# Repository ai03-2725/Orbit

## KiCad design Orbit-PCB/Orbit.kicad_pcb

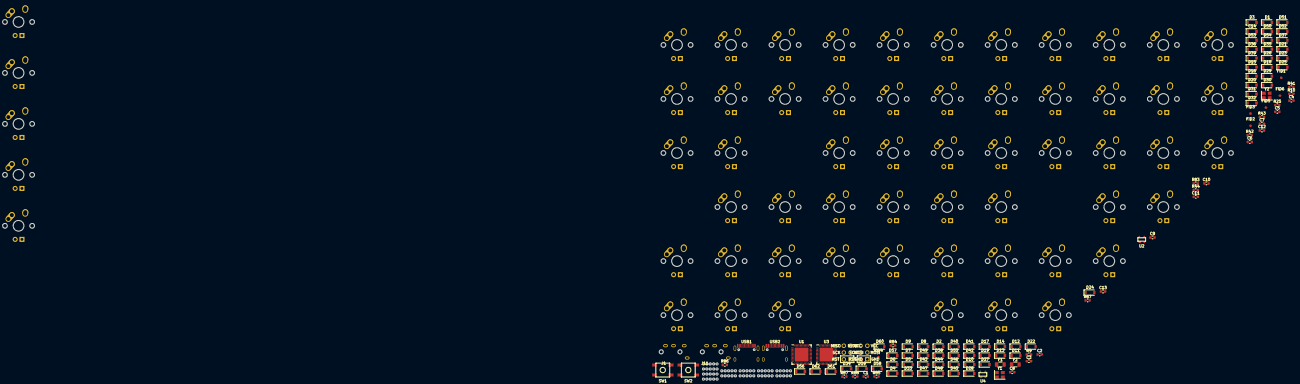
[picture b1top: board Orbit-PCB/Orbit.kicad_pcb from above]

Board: 2 copper layers, 184 parts (0 on the bottom side), 124 nets, no tracks yet.

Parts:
C1, C2, C8, C9: 22pF; C_0603_1608Metric
C3, C10: 1uF; C_0603_1608Metric
C4, C5, C6, C11, C12, C13: 0.1uF; C_0603_1608Metric
C7: 10uF; C_0603_1608Metric
C14: 10uF; D_SOD-123
D1, D2: Schottky; D_SOD-123
D3, D4, D5, D6, D7, D8, D9, D10, D11, D12, D13, D14, D15, D16, D17, D18, D19, D20, D21, D22, D23, D24, D25, D26, D27, D28, D29, D30, D31, D32, D33, D34, D35, D36, D37, D38, D39, D40, D41, D42, D43, D44, D45, D46, D47, D48, D49, D50, D51, D52, D53, D54, D55, D56, D57, D58, D59, D60, D61, D62: SOD-123; D_SOD-123
F1, F2: 500mA; Fuse_1206_3216Metric
FID1, FID2, FID3, FID4, FID5, FID6: Fiducial; Fiducial_1mm_Mask3mm
J1, J11: PJ-3200B-4A
J2, J12: AVR-ISP-6; Reset_Pretty-Mask
J3, J5, J6, J7, J9, J10, J13, J14, J17, J18, J19, J20: Breakaway_Tabs; breakaway-mousebites
MX1, MX2, MX3, MX4, MX5, MX6, MX7, MX8, MX9, MX10, MX11, MX12, MX13, MX14, MX15, MX16, MX17, MX18, MX19, MX20, MX21, MX22, MX23, MX24, MX25, MX26, MX27, MX28, MX29, MX30, MX31, MX32, MX33, MX34, MX35, MX36, MX37, MX38, MX39, MX40, MX41, MX42, MX43, MX44, MX45, MX46, MX47, MX48, MX49, MX50, MX51, MX52, MX53, MX54, MX55, MX56, MX57, MX58, MX59, MX60: MX-1U
R9, R10: 4.7k; R_0603_1608Metric
R25, R67, R87, R88: 10k; R_0603_1608Metric
R41, R42, R83, R84: 22; R_0603_1608Metric
R43, R44, R85, R86: 5.1k; R_0603_1608Metric
SW1, SW2: SW_Push; SKQGADE010
U1, U3: ATmega32U4-MU; QFN-44-1EP_7x7mm_P0.5mm_EP5.15x5.15mm
U2, U4: PRTR5V0U2X; SOT143B
USB1, USB2: HRO-TYPE-C-31-M-12; HRO-TYPE-C-31-M-12-Assembly
Y1, Y2: 16MHz; Crystal_SMD_3225-4Pin_3.2x2.5mm

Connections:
+5V: C4.1, C5.1, C6.1, C7.1, D1.1, J1.4, J2.2, R9.1, R10.1, R87.1, U1.14, U1.24, U1.34, U1.44
+5VA: C11.1, C12.1, C13.1, C14.1, D2.1, J11.4, J12.2, U3.14, U3.24, U3.34, U3.44
COL0: MX1.1, MX7.1, MX13.1, MX19.1, MX25.1, U1.32
COL0-R: MX31.1, MX37.1, MX43.1, MX49.1, MX55.1, U3.25
COL1: MX2.1, MX8.1, MX14.1, MX20.1, MX26.1, U1.28
COL1-R: MX32.1, MX38.1, MX44.1, MX50.1, MX56.1, U3.26
COL2: MX3.1, MX9.1, MX15.1, MX21.1, MX27.1, U1.27
COL2-R: MX33.1, MX39.1, MX45.1, MX51.1, MX57.1, U3.40
COL3: MX4.1, MX10.1, MX16.1, MX22.1, MX28.1, U1.26
COL3-R: MX34.1, MX40.1, MX46.1, MX52.1, MX58.1, U3.41
COL4: MX5.1, MX11.1, MX17.1, MX23.1, MX29.1, U1.25
COL4-R: MX35.1, MX41.1, MX47.1, MX53.1, MX59.1, U3.39
COL5: MX6.1, MX12.1, MX18.1, MX24.1, MX30.1, U1.40
COL5-R: MX36.1, MX42.1, MX48.1, MX54.1, MX60.1, U3.38
D+: R41.1, U1.4
D+-R: R83.1, U3.4
D-: R42.1, U1.3
D--R: R84.1, U3.3
GND: C1.2, C2.2, C3.2, C4.2, C5.2, C6.2, C7.2, J1.1, J2.6, R25.1, R43.2, R44.2, SW1.1, U1.5, U1.15, U1.23, U1.35, U1.43, U1.45, U2.1, USB1.1, USB1.12, USB1.13, Y1.2, Y1.4
GNDA: C8.2, C9.2, C10.2, C11.2, C12.2, C13.2, C14.2, J11.1, J12.6, R67.1, R85.2, R86.2, R88.1, SW2.1, U3.5, U3.15, U3.23, U3.35, U3.43, U3.45, U4.1, USB2.1, USB2.12, USB2.13, Y2.2, Y2.4
HDETECT: R87.2, U1.22
HDETECT-R: R88.2, U3.22
MISO: J2.1, U1.11
MISO-R: J12.1, U3.11
MOSI: J2.4, U1.10
MOSI-R: J12.4, U3.10
unnamed: C1.1, U1.17, Y1.1
unnamed: C2.1, U1.16, Y1.3
unnamed: C3.1, U1.6
unnamed: C8.1, U3.17, Y2.1
unnamed: C9.1, U3.16, Y2.3
unnamed: C10.1, U3.6
unnamed: D3.2, MX1.2
unnamed: D4.2, MX2.2
unnamed: D5.2, MX3.2
unnamed: D6.2, MX4.2
unnamed: D7.2, MX5.2
unnamed: D8.2, MX6.2
unnamed: D9.2, MX7.2
unnamed: D10.2, MX8.2
unnamed: D11.2, MX9.2
unnamed: D12.2, MX10.2
unnamed: D13.2, MX11.2
unnamed: D14.2, MX12.2
unnamed: D15.2, MX13.2
unnamed: D16.2, MX14.2
unnamed: D17.2, MX15.2
unnamed: D18.2, MX16.2
unnamed: D19.2, MX17.2
unnamed: D20.2, MX18.2
unnamed: D21.2, MX19.2
unnamed: D22.2, MX20.2
unnamed: D23.2, MX21.2
unnamed: D24.2, MX22.2
unnamed: D25.2, MX23.2
unnamed: D26.2, MX24.2
unnamed: D27.2, MX25.2
unnamed: D28.2, MX26.2
unnamed: D29.2, MX27.2
unnamed: D30.2, MX28.2
unnamed: D31.2, MX29.2
unnamed: D32.2, MX30.2
unnamed: D33.2, MX31.2
unnamed: D34.2, MX32.2
unnamed: D35.2, MX33.2
unnamed: D36.2, MX34.2
unnamed: D37.2, MX35.2
unnamed: D38.2, MX36.2
unnamed: D39.2, MX37.2
unnamed: D40.2, MX38.2
unnamed: D41.2, MX39.2
unnamed: D42.2, MX40.2
unnamed: D43.2, MX41.2
unnamed: D44.2, MX42.2
unnamed: D45.2, MX43.2
unnamed: D46.2, MX44.2
unnamed: D47.2, MX45.2
unnamed: D48.2, MX46.2
unnamed: D49.2, MX47.2
unnamed: D50.2, MX48.2
unnamed: D51.2, MX49.2
unnamed: D52.2, MX50.2
unnamed: D53.2, MX51.2
unnamed: D54.2, MX52.2
unnamed: D55.2, MX53.2
unnamed: D56.2, MX54.2
unnamed: D57.2, MX55.2
unnamed: D58.2, MX56.2
unnamed: D59.2, MX57.2
unnamed: D60.2, MX58.2
unnamed: D61.2, MX59.2
unnamed: D62.2, MX60.2
unnamed: R25.2, U1.33
unnamed: R41.2, U2.2, USB1.6, USB1.8
unnamed: R42.2, U2.3, USB1.5, USB1.7
unnamed: R43.1, USB1.10
unnamed: R44.1, USB1.4
unnamed: R67.2, U3.33
unnamed: R83.2, U4.2, USB2.6, USB2.8
unnamed: R84.2, U4.3, USB2.5, USB2.7
unnamed: R85.1, USB2.10
unnamed: R86.1, USB2.4
RESET: J2.5, SW1.2, U1.13
RESET-R: J12.5, SW2.2, U3.13
ROW0: D3.1, D4.1, D5.1, D6.1, D7.1, D8.1, U1.36
ROW0-R: D33.1, D34.1, D35.1, D36.1, D37.1, D38.1, U3.30
ROW1: D9.1, D10.1, D11.1, D12.1, D13.1, D14.1, U1.37
ROW1-R: D39.1, D40.1, D41.1, D42.1, D43.1, D44.1, U3.29
ROW2: D15.1, D16.1, D17.1, D18.1, D19.1, D20.1, U1.38
ROW2-R: D45.1, D46.1, D47.1, D48.1, D49.1, D50.1, U3.28
ROW3: D21.1, D22.1, D23.1, D24.1, D25.1, D26.1, U1.39
ROW3-R: D51.1, D52.1, D53.1, D54.1, D55.1, D56.1, U3.27
ROW4: D28.1, D29.1, D30.1, D31.1, D32.1, U1.21
ROW4-R: D58.1, D59.1, D60.1, D61.1, D62.1, U3.1
SCK: J2.3, U1.9
SCK-R: J12.3, U3.9
SCL: J1.2, R10.2, U1.18
SCL-R: J11.2, U3.18
SDA: J1.3, R9.2, U1.19
SDA-R: J11.3, U3.19
VBUS: D1.2, F1.1, U1.2, U1.7
VCC: F1.2, U2.4, USB1.2, USB1.11
VDC: D2.2, F2.1, U3.2, U3.7
VDD: F2.2, U4.4, USB2.2, USB2.11

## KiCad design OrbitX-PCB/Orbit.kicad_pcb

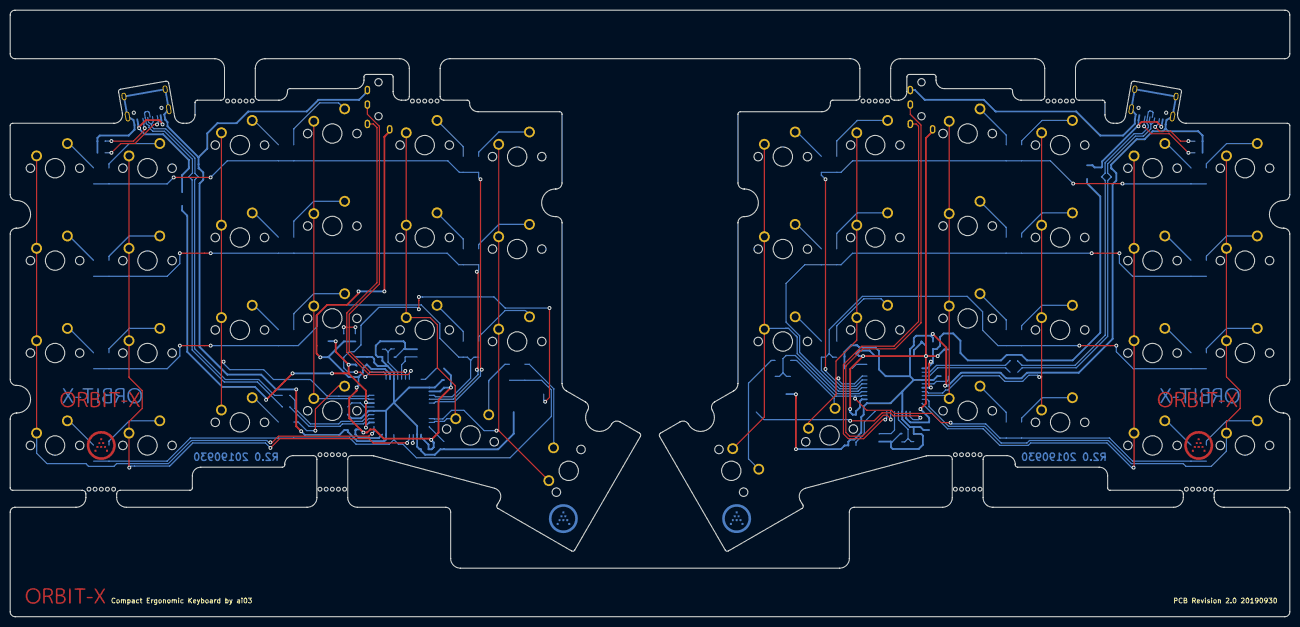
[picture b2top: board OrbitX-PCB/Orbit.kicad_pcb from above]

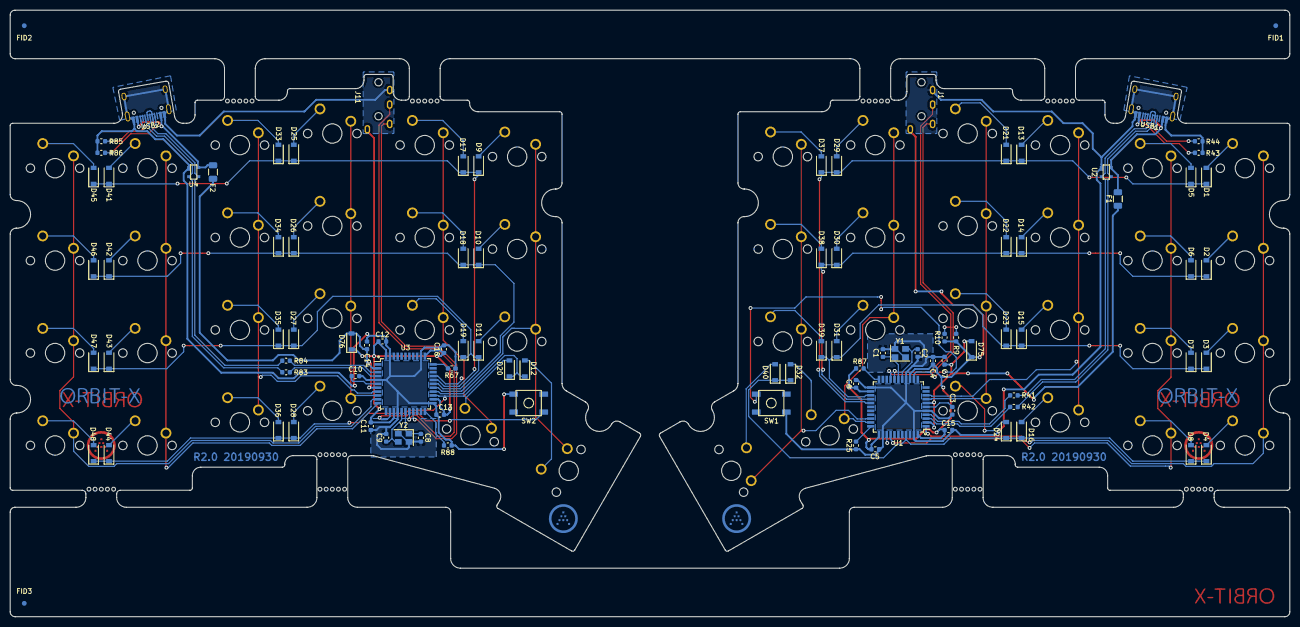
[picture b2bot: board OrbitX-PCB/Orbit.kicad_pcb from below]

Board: 2 copper layers, 263.8 x 125.0 mm, 155 parts (97 on the bottom side), 104 nets.

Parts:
C1, C2, C8, C9: 22pF; C_0603_1608Metric
C3, C10: 1uF; C_0603_1608Metric
C4, C5, C6, C11, C12, C13, C15, C16: 0.1uF; C_0603_1608Metric
C7, C14: 10uF; C_0603_1608Metric
D1, D2, D3, D4, D5, D6, D7, D8, D9, D10, D11, D12, D13, D14, D15, D16, D17, D18, D19, D20, D21, D22, D23, D24, D25, D26, D27, D28, D29, D30, D31, D32, D33, D34, D35, D36, D37, D38, D39, D40, D41, D42, D43, D44, D45, D46, D47, D48: SOD123; D_SOD-123
D75, D76: Schottky; D_SOD-123
F1, F2: 500mA; Fuse_1206_3216Metric
FID1, FID2, FID3: Fiducial; Fiducial_1mm_Dia_2.54mm_Outer_CopperTop
J1, J11: PJ-3200B-4A
J3, J5, J6, J7, J9, J13, J14, J17, J18, J19: Breakaway_Tabs; breakaway-mousebites
MX1, MX2, MX3, MX4, MX5, MX6, MX7, MX8, MX9, MX10, MX11, MX13, MX14, MX15, MX16, MX17, MX18, MX19, MX20, MX21, MX22, MX23, MX24, MX25, MX26, MX27, MX28, MX29, MX30, MX31, MX32, MX33, MX34, MX35, MX36, MX37, MX38, MX39, MX41, MX42, MX43, MX44, MX45, MX46, MX47, MX48: MX-NoLED; MXOnly-1U-NoLED
MX12, MX40: MX-NoLED; MXOnly-1.5U-NoLED
R9, R10: 4.7k; R_0603_1608Metric
R25, R67, R87, R88: 10k; R_0603_1608Metric
R41, R42, R83, R84: 22; R_0603_1608Metric
R43, R44, R85, R86: 5.1k; R_0603_1608Metric
SW1, SW2: SW_Push; SKQGADE010
U1, U3: ATmega32U4-AU; TQFP-44_10x10mm_P0.8mm
U2, U4: PRTR5V0U2X; SOT143B
USB1, USB2: HRO-TYPE-C-31-M-12; HRO-TYPE-C-31-M-12-Assembly
Y1, Y2: 16MHz; Crystal_SMD_3225-4Pin_3.2x2.5mm

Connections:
+5V: C4.1, C5.1, C6.1, C15.1, D75.1, J1.4, R9.1, R10.1, R87.1, U1.14, U1.24, U1.34, U1.44
+5VA: C11.1, C12.1, C13.1, C16.1, D76.1, J11.4, U3.14, U3.24, U3.34, U3.44
COL0: MX1.1, MX2.1, MX3.1, MX4.1, U1.1
COL0-R: MX9.1, MX10.1, MX11.1, MX12.1, U3.26
COL1: MX5.1, MX6.1, MX7.1, MX8.1, U1.37
COL1-R: MX17.1, MX18.1, MX19.1, MX20.1, U3.30
COL2: MX13.1, MX14.1, MX15.1, MX16.1, U1.9
COL2-R: MX25.1, MX26.1, MX27.1, MX28.1, U3.9
COL3: MX21.1, MX22.1, MX23.1, MX24.1, U1.8
COL3-R: MX33.1, MX34.1, MX35.1, MX36.1, U3.8
COL4: MX29.1, MX30.1, MX31.1, MX32.1, U1.32
COL4-R: MX41.1, MX42.1, MX43.1, MX44.1, U3.11
COL5: MX37.1, MX38.1, MX39.1, MX40.1, U1.31
COL5-R: MX45.1, MX46.1, MX47.1, MX48.1, U3.10
D+: R41.1, U1.4
D+-R: R83.1, U3.4
D-: R42.1, U1.3
D--R: R84.1, U3.3
GND: C1.2, C2.2, C3.2, C4.2, C5.2, C6.2, C7.2, C15.2, J1.1, R25.1, R43.2, R44.2, SW1.1, U1.5, U1.15, U1.23, U1.35, U1.43, U2.1, USB1.1, USB1.12, USB1.13, Y1.2, Y1.4
GNDA: C8.2, C9.2, C10.2, C11.2, C12.2, C13.2, C14.2, C16.2, J11.1, R67.1, R85.2, R86.2, R88.1, SW2.1, U3.5, U3.15, U3.23, U3.35, U3.43, U4.1, USB2.1, USB2.12, USB2.13, Y2.2, Y2.4
HDETECT: R87.2, U1.22
HDETECT-R: R88.2, U3.22
unnamed: C1.1, U1.17, Y1.1
unnamed: C2.1, U1.16, Y1.3
unnamed: C3.1, U1.6
unnamed: C8.1, U3.17, Y2.1
unnamed: C9.1, U3.16, Y2.3
unnamed: C10.1, U3.6
unnamed: D1.2, MX1.2
unnamed: D2.2, MX2.2
unnamed: D3.2, MX3.2
unnamed: D4.2, MX4.2
unnamed: D5.2, MX5.2
unnamed: D6.2, MX6.2
unnamed: D7.2, MX7.2
unnamed: D8.2, MX8.2
unnamed: D9.2, MX9.2
unnamed: D10.2, MX10.2
unnamed: D11.2, MX11.2
unnamed: D12.2, MX12.2
unnamed: D13.2, MX13.2
unnamed: D14.2, MX14.2
unnamed: D15.2, MX15.2
unnamed: D16.2, MX16.2
unnamed: D17.2, MX17.2
unnamed: D18.2, MX18.2
unnamed: D19.2, MX19.2
unnamed: D20.2, MX20.2
unnamed: D21.2, MX21.2
unnamed: D22.2, MX22.2
unnamed: D23.2, MX23.2
unnamed: D24.2, MX24.2
unnamed: D25.2, MX25.2
unnamed: D26.2, MX26.2
unnamed: D27.2, MX27.2
unnamed: D28.2, MX28.2
unnamed: D29.2, MX29.2
unnamed: D30.2, MX30.2
unnamed: D31.2, MX31.2
unnamed: D32.2, MX32.2
unnamed: D33.2, MX33.2
unnamed: D34.2, MX34.2
unnamed: D35.2, MX35.2
unnamed: D36.2, MX36.2
unnamed: D37.2, MX37.2
unnamed: D38.2, MX38.2
unnamed: D39.2, MX39.2
unnamed: D40.2, MX40.2
unnamed: D41.2, MX41.2
unnamed: D42.2, MX42.2
unnamed: D43.2, MX43.2
unnamed: D44.2, MX44.2
unnamed: D45.2, MX45.2
unnamed: D46.2, MX46.2
unnamed: D47.2, MX47.2
unnamed: D48.2, MX48.2
unnamed: R25.2, U1.33
unnamed: R41.2, U2.2, USB1.6, USB1.8
unnamed: R42.2, U2.3, USB1.5, USB1.7
unnamed: R43.1, USB1.10
unnamed: R44.1, USB1.4
unnamed: R67.2, U3.33
unnamed: R83.2, U4.2, USB2.6, USB2.8
unnamed: R84.2, U4.3, USB2.5, USB2.7
unnamed: R85.1, USB2.10
unnamed: R86.1, USB2.4
RESET: SW1.2, U1.13
RESET-R: SW2.2, U3.13
ROW0: D1.1, D5.1, D13.1, D21.1, D29.1, D37.1, U1.27
ROW0-R: D9.1, D17.1, D25.1, D33.1, D41.1, D45.1, U3.29
ROW1: D2.1, D6.1, D14.1, D22.1, D30.1, D38.1, U1.26
ROW1-R: D10.1, D18.1, D26.1, D34.1, D42.1, D46.1, U3.27
ROW2: D3.1, D7.1, D15.1, D23.1, D31.1, D39.1, U1.25
ROW2-R: D11.1, D19.1, D27.1, D35.1, D43.1, D47.1, U3.28
ROW3: D4.1, D8.1, D16.1, D24.1, D32.1, D40.1, U1.41
ROW3-R: D12.1, D20.1, D28.1, D36.1, D44.1, D48.1, U3.25
SCL: J1.2, R10.2, U1.18
SCL-R: J11.2, U3.18
SDA: J1.3, R9.2, U1.19
SDA-R: J11.3, U3.19
VBUS: C7.1, D75.2, F1.1, U1.2, U1.7
VCC: F1.2, U2.4, USB1.2, USB1.11
VDC: C14.1, D76.2, F2.1, U3.2, U3.7
VDD: F2.2, U4.4, USB2.2, USB2.11

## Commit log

2019-09-30 Progress save
2019-10-01 Build new OrbitX PCB
2019-10-01 Finalize decal
2019-10-01 Generate gerber
2019-11-10 JLC files
2020-03-30 Update orbit-x to production copy
